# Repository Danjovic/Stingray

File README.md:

# Stingray
Nintendo Classic controller adapter with keypad emulation for Atari 5200

 This project This adapter lets you play Atari 5200 using a Wii Classic controller yet providing full keypad control.
 
Main features are 

-Analog Controller (using precise timing);
-Digital Controller on D-PAD just like a Masterplay adapter;
-Full keypad emulation;
-Auto detected second controller adapter for games like Robotron
-Independent Top/Bottom buttons on second controller. 
	
The circuit is built around an Arduino Nano and two analog multiplexers. 

Interface with Nintendo Classic controller uses I2C communication. Analog joystick information is provided to Atari 5200 using the "time precise" method and uses the internal Analog Comparator of the AVR to detect the moment the Pokey chip releases the capacitors to charge and starts counting time.

The analog multiplexers are used to emulate one of the 15 possible keys pressed. Buttons and controllers are mapped as follows:

The adapter for the second controller consists in a USB cord with a Male USB type A in one edge and a DB-15 female connector on another. The wiring is below:

The circuit also provides a mini-DIN connector with pull up resistors. At the moment this is a provision for emulation of trackball using a PS/2 mouse.

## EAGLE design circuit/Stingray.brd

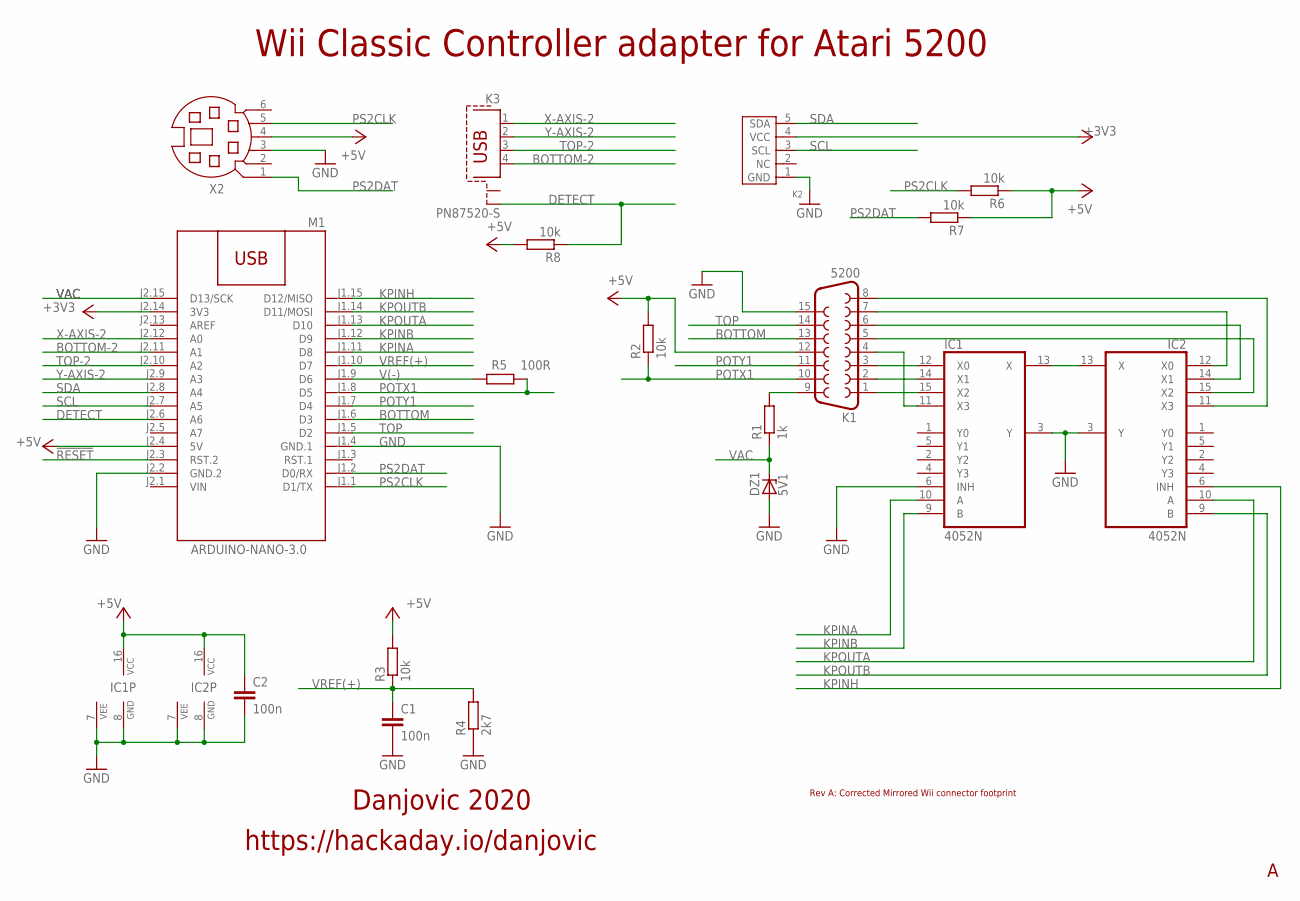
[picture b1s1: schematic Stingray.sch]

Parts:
C1, C2: 100n; C050-024X044
DZ1: 5V1; ZDIO-7.5
IC1, IC2: 4052N; DIL16
K1: 5200; F15D
K2: WIICHUCK
K3: PN87520-S
M1: ARDUINO-NANO-3.0
R1: 1k; 0204/7
R2, R3, R6, R7, R8: 10k; 0204/7
R4: 2k7; 0204/7
R5: 100R; 0204/7
X2: MD06SS; MDIN06SS

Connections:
!RESET: M1.J2.3 (RST.2)
+3V3: K2.4 (VCC), M1.J2.14 (3V3)
+5V: C2.1, IC1.16 (VCC), IC2.16 (VCC), K1.12, M1.J2.4 (5V), R2.2, R3.2, R6.1, R7.1, R8.2, X2.4
BOTTOM: K1.13, M1.J1.6 (D3)
BOTTOM-2: K3.4, M1.J2.11 (A1)
COL0: IC2.12 (X0), K1.7
COL1: IC2.14 (X1), K1.6
COL2: IC2.15 (X2), K1.5
COL3: IC2.11 (X3), K1.8
DETECT: K3.S2, M1.J2.6 (A6), R8.1
GND: C1.2, C2.2, DZ1.A, IC1.3 (Y), IC1.6 (INH), IC1.7 (VEE), IC1.8 (GND), IC2.3 (Y), IC2.7 (VEE), IC2.8 (GND), K1.15, K2.1 (GND), M1.J1.4 (GND.1), M1.J2.2 (GND.2), R4.1, X2.3
KPINA: IC1.10 (A), M1.J1.11 (D8)
KPINB: IC1.9 (B), M1.J1.12 (D9)
KPINH: IC2.6 (INH), M1.J1.15 (D12/MISO)
KPOUTA: IC2.10 (A), M1.J1.13 (D10)
KPOUTB: IC2.9 (B), M1.J1.14 (D11/MOSI)
unnamed: K1.9, R1.2
POTX1: K1.10, M1.J1.8 (D5), R2.1, R5.1
POTY1: K1.11, M1.J1.7 (D4)
PS2CLK: M1.J1.1 (D1/TX), R6.2, X2.5
PS2DAT: M1.J1.2 (D0/RX), R7.2, X2.1
ROW0: IC1.12 (X0), K1.3
ROW1: IC1.14 (X1), K1.2
ROW2: IC1.15 (X2), K1.1
ROW3: IC1.11 (X3), K1.4
SCL: K2.3 (SCL), M1.J2.7 (A5)
SDA: K2.5 (SDA), M1.J2.8 (A4)
TOP: K1.14, M1.J1.5 (D2)
TOP-2: K3.3, M1.J2.10 (A2)
V(-): M1.J1.9 (D6), R5.2
VAC: DZ1.C, M1.J2.15 (D13/SCK), R1.1
VIN: M1.J2.1 (VIN)
VREF(+): C1.1, M1.J1.10 (D7), R3.1, R4.2
X-AXIS-2: K3.1, M1.J2.12 (A0)
XX: IC1.13 (X), IC2.13 (X)
Y-AXIS-2: K3.2, M1.J2.9 (A3)

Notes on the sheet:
Wii Classic Controller adapter for Atari 5200
Danjovic 2020
https://hackaday.io/danjovic
Rev A: Corrected Mirrored Wii connector footprint

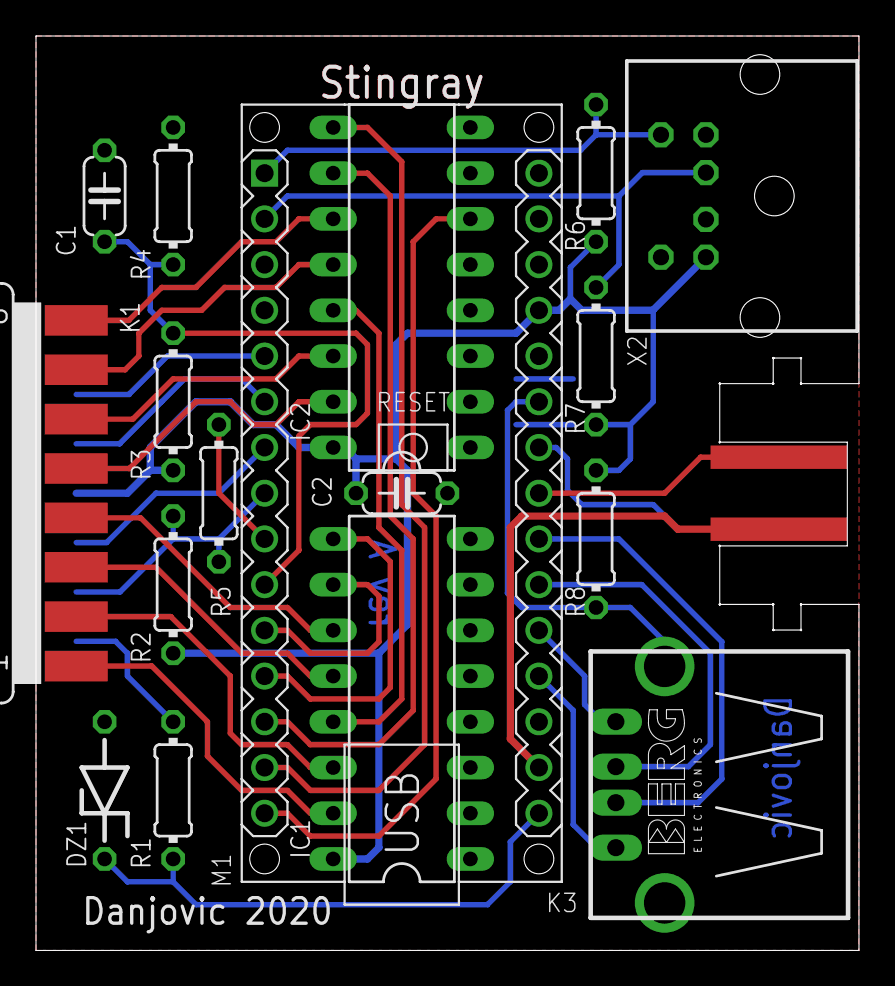
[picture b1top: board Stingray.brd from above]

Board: 2 copper layers, 45.7 x 50.8 mm, 18 parts (1 on the bottom side), 34 nets.

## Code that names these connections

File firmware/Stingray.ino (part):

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#define outputMuxB        11
#define outputMuxInhibt   12

#define potX1             5 
#define potY1             4 
#define fireTop1          3 
#define fireBottom1       2 

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 *     |_|_|_\__,_\__|_| \___/__/ 
 *                                
 */
#define pushX1() do { pinMode(potX1,OUTPUT); digitalWrite(potX1,HIGH); } while (0)
#define pushX2() do { pinMode(potX2,OUTPUT); digitalWrite(potX2,HIGH); } while (0)
#define pushY1() do { pinMode(potY1,OUTPUT); digitalWrite(potY1,HIGH); } while (0)
#define pushY2() do { pinMode(potY2,OUTPUT); digitalWrite(potY2,HIGH); } while (0)


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ISR (PCINT0_vect) {
	if (digitalRead(caVinput)) {  // rising edge ?
       // Enable detection of pokey release pin for charging
       pinMode(potX1,INPUT); 
	   pinMode(potX2,INPUT); 
	   pinMode(potY1,INPUT);	   
	   pinMode(potY2,INPUT);
       CAVoff = 0;	  // flag that CAV voltage is present 	   
       ACSR |= (1<<ACIE)  // reactivate analog comparator
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       hline++;
      
    } else if (hline==227) {
       //last line, release all pins to make possible to detect next discharge
       pinMode(potX1,INPUT); 
	   pinMode(potX2,INPUT); 
	   pinMode(potY1,INPUT);	   
	   pinMode(potY2,INPUT);	

       ACSR |= (1<<ACIE)  // reactivate analog comparator
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// Analog comparator, triggers when detect that pokey released POT inputs to charge
ISR (ANALOG_COMP_vect) {
//  pulseFlag();    
  pinMode(potX1,OUTPUT);   // hold axis pin in LOW state
  digitalWrite(potX1,LOW); 

  hline=0;
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  pinMode(fireTop2    ,INPUT) ;
  pinMode(fireBottom2 ,INPUT) ;  
  
  pinMode(potX1,INPUT) ; // Potentiometer pins as inputs 
  pinMode(potY1,INPUT) ; 
  pinMode(potX2,INPUT) ;
  pinMode(potY2,INPUT) ;
  
  digitalWrite(potX1,LOW); // disable pullups on potentiometer pins 
  digitalWrite(potX2,LOW); 
  digitalWrite(potY1,LOW); 
  digitalWrite(potY2,LOW); 
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         | (0<<PCINT2)  // Pin change enable for PB2 pin 
         | (0<<PCINT3)  // Pin change enable for PB3 pin 
         | (0<<PCINT4)  // Pin change enable for PB4 pin 
         | (1<<PCINT5)  // Pin change enable for PB5 pin - Vac voltage is connected here
         | (0<<PCINT6)  // Pin change enable for PB6 pin 
         | (0<<PCINT7); // Pin change enable for PB7 pin   

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
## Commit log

2020-03-14 Added PCB files and button mapping documentation
2020-03-22 added files via upload
2020-03-22 update files
2020-03-24 Alpha release, Joystick control seems fine, keyboard emulation to be tested.
2020-03-26 Beta Version, functional yet prone to improvements
2020-08-27 Corrected mirrored Wii connector footprint
2020-08-27 Corrected bug: disableOutputs() doing nothing when not in debug mode
2021-03-21 Bug fixes and code improvement
2021-03-21 Updated value of R1 to 1K

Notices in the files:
firmware/Stingray.ino:
This program is free software: you can redistribute it and/or modify
it under the terms of the GNU General Public License as published by
the Free Software Foundation, either version 3 of the License, or
(at your option) any later version.
parts and their libraries:
diy-modules: Released under the Creative Commons Attribution 4.0 International License: http://creativecommons.org/licenses/by/4.0
SparkFun-Aesthetics: Licensing: Creative Commons ShareAlike 4.0 International - https://creativecommons.org/licenses/by-sa/4.0
